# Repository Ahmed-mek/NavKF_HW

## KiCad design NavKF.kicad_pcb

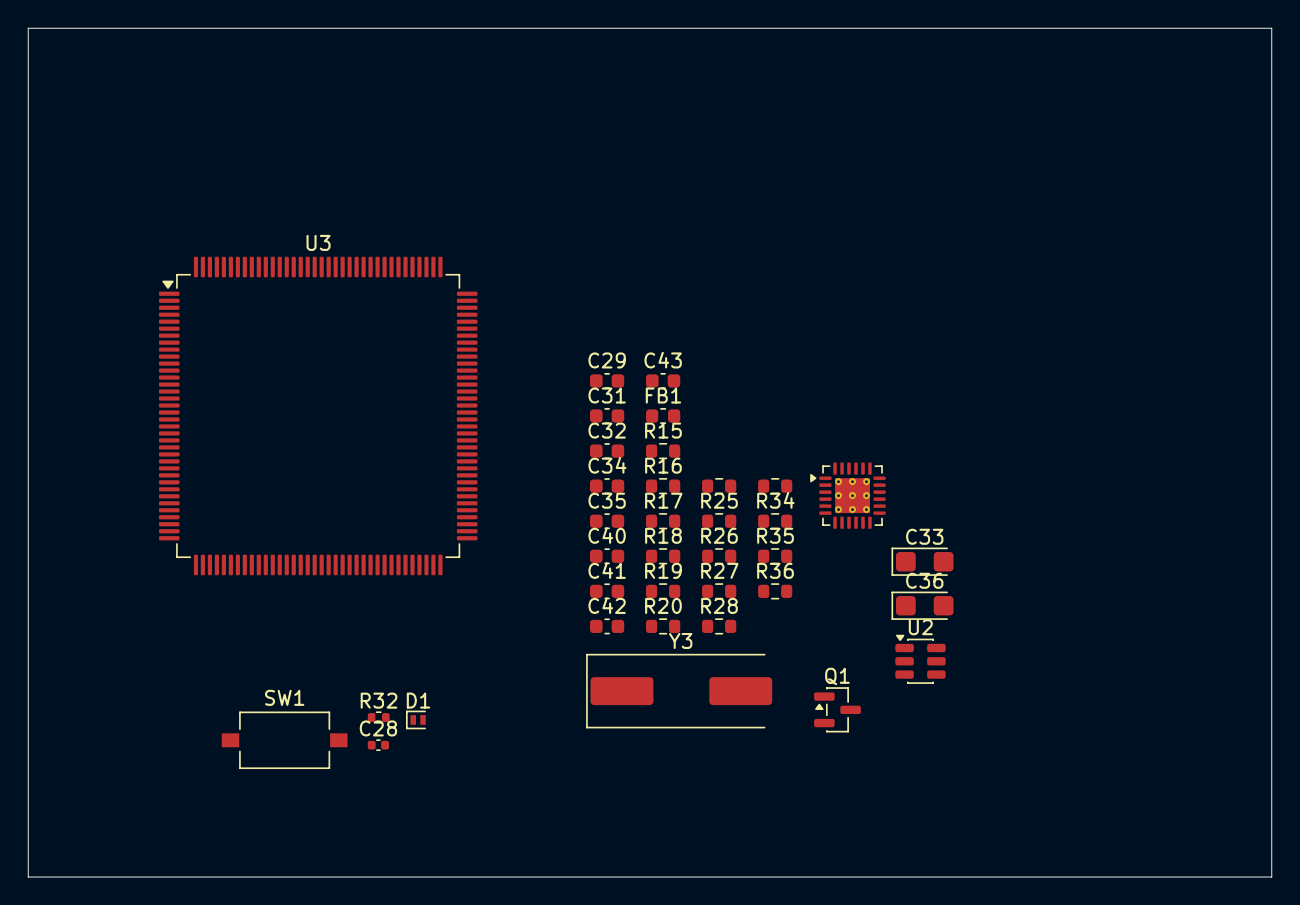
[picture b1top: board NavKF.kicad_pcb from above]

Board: 2 copper layers, 89.0 x 60.8 mm, 36 parts (0 on the bottom side), 19 nets, no tracks yet.

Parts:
C28: 100nF; C_0402_1005Metric
C29: 1uF/25V; C_0603_1608Metric
C31: 470pF; C_0603_1608Metric
C32, C34, C35, C40, C41, C42, C43: 100nF; C_0603_1608Metric
C33, C36: 10uF; CP_EIA-3216-18_Kemet-A
D1: ESDALC6V1; D_SOD-882
FB1: 600R@100MHz; L_0603_1608Metric
Q1: BC817; SOT-23
R15, R17, R18: 33R; R_0603_1608Metric
R16: 1K5; R_0603_1608Metric
R19, R20, R24, R26, R27: 10K; R_0603_1608Metric
R25, R33, R35: 270R; R_0603_1608Metric
R28: 12K1; R_0603_1608Metric
R32: 10K; R_0402_1005Metric
R34, R36: 49.9Ω; R_0603_1608Metric
SW1: Reset; SW_Tactile_SPST_NO_Straight_CK_PTS636Sx25SMTRLFS
U2: USBLC6-4SC6; SOT-23-6
U3: STM32H723ZGTx; LQFP-144_20x20mm_P0.5mm
U4: LAN8742A; VQFN-24-1EP_4x4mm_P0.5mm_EP2.5x2.5mm_ThermalVias
Y3: 25MHZ; Crystal_SMD_HC49-SD

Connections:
+3V0: C32.1, C33.1, FB1.2, R34.1, R36.1, U4.1 (VDD2A), U4.19 (VDD1A)
/Ethernet/3V3_PER: C34.1, C35.1, C36.1, C40.1, C41.1, FB1.1, R16.1, R19.2, R20.2, R27.2, U4.9 (VDDIO)
/Ethernet/RMII_MDIO: R16.2, U4.12 (MDIO)
/Ethernet/TD_N: R34.2, U4.20 (TXN)
/Ethernet/TD_P: R36.2, U4.21 (TXP)
/Ethernet/VDDCR: C29.1, C31.1, U4.6 (VDDCR)
/Ethernet/nRST_E: Q1.3 (C), R27.1, U4.15 (~RST)
/Ethernet/rxi+: R17.2, U4.8 (RXD0/MODE0)
/Ethernet/rxi-: R18.2, R19.1, U4.7 (RXD1/MODE1)
/MCU/NRST: C28.1, D1.1 (K), SW1.1 (A), SW1.2 (A)
GND: C28.2, C29.2, C31.2, C32.2, C33.2, C34.2, C35.2, C36.2, C40.2, C41.2, C42.2, C43.2, D1.2 (A), Q1.2 (E), R24.1, R26.1, R28.2, R33.2, R35.2, U4.25 (VSS)
unnamed: C42.1, C43.1
unnamed: Q1.1 (B), R25.1, R26.2
unnamed: U3.16 (VSS), U3.38 (VSS), U3.51 (VSS), U3.61 (VSS), U3.83 (VSS), U3.94 (VSS), U3.107 (VSS), U3.120 (VSS), U3.130 (VSS)
unnamed: R28.1, U4.24 (RBIAS)
unnamed: R24.2, U4.10 (RXER/PHYAD0)
unnamed: U4.5 (XTAL1/CLKIN), Y3.2
unnamed: U4.4 (XTAL2), Y3.1
unnamed: R15.2, R20.1, U4.14 (~INT/REFCLKO)

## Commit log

2026-04-17 init
2026-04-17 test1
2026-05-07 Ignore KiCad lock files
2026-05-07 KiCad: update NavKF
2026-05-07 Remove .history and lock files
2026-05-07 KiCad: update NavKF
    [Version: v1.0.1] [Date: 2026-05-07T15:09:48+03:00]
2026-05-07 KiCad: update NavKF
    [Version: v1.0.2] [Date: 2026-05-07T15:10:53+03:00]
2026-05-07 KiCad: update NavKF
    [Version: v1.0.1] [Date: 2026-05-07 15:20:30]
2026-05-07 LIB: update symbols/footprints
    [Version: v1.0.1] [Date: 2026-05-07 15:33:30]
2026-05-08 Chore: project cleanup
    [Revision: REV-15] [Date: 2026-05-08 17:35:14]
